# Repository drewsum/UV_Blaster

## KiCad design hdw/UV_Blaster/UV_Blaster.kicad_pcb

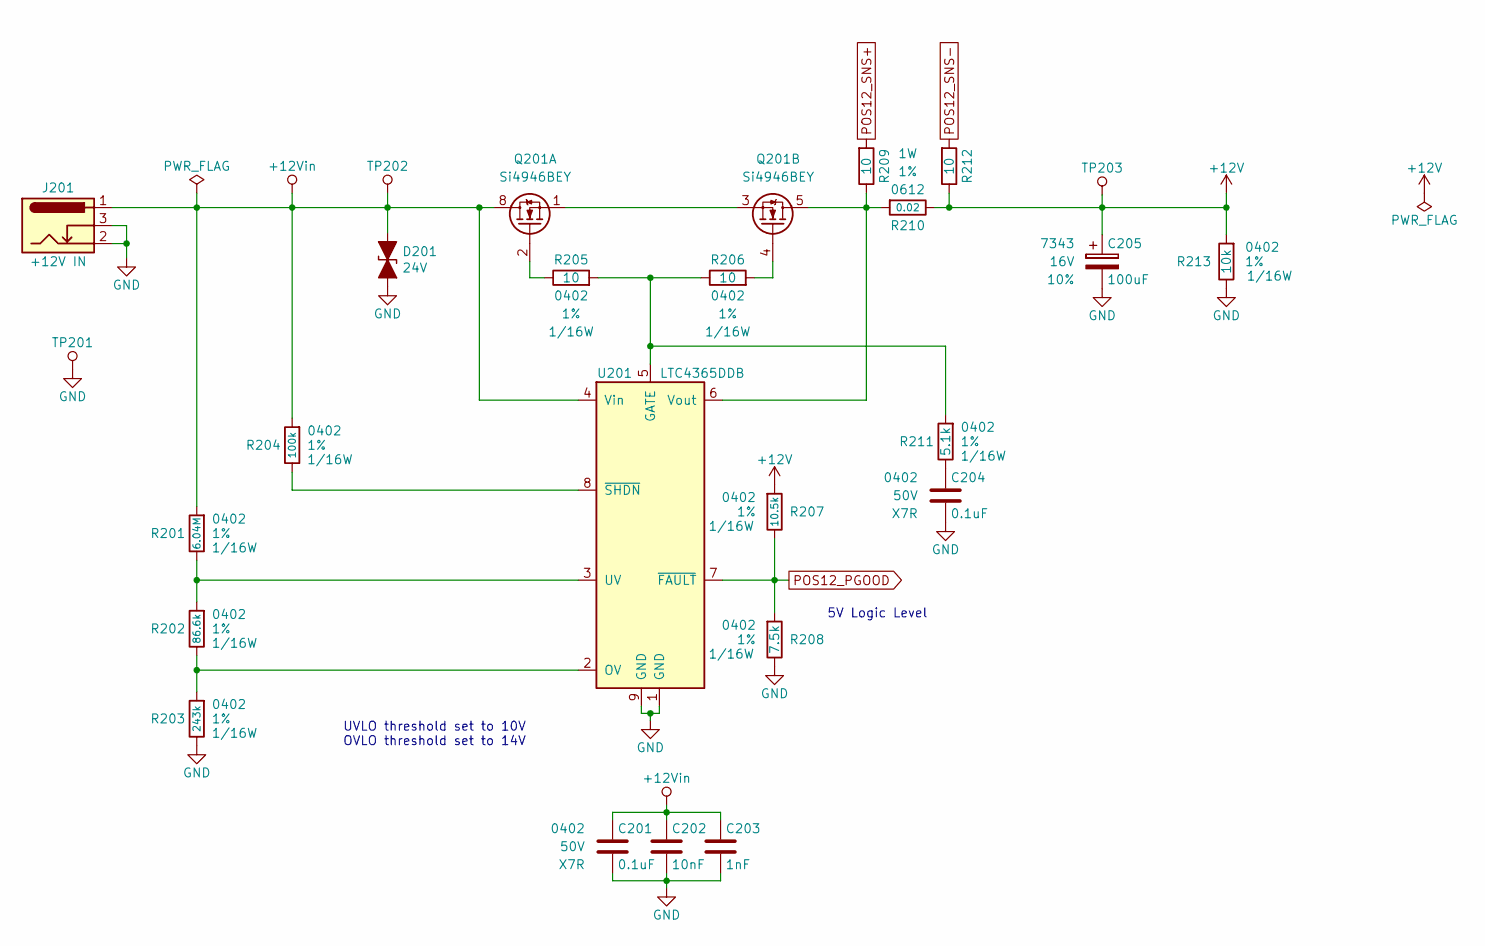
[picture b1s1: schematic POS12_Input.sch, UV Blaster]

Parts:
C201, C204: 0.1uF; C_0402; Voltage 50V; Digi-Key PN 490-10701-1-ND
C202: 10nF; C_0402; Voltage 50V; Digi-Key PN 490-13295-1-ND
C203: 1nF; C_0402; Voltage 50V; Digi-Key PN 399-1032-1-ND
C205: 100uF; CP_Tantalum_Case-X_EIA-7343-43_Reflow; Voltage 16V; Tolerance 10%; Digi-Key PN 718-1102-1-ND
D201: 24V; D_SMA; Digi-Key PN SMAJ24CALFCT-ND
J201: +12V IN; BARREL_JACK
Q201: Si4946BEY; SOIC-8_3.9x4.9mm_P1.27mm; Digi-Key PN SI4946BEY-T1-E3CT-ND
R201: 6.04M; R_0402; Tolerance 1%; Digi-Key PN 541-CRCW04026M04FKEDCT-ND
R202: 86.6k; R_0402; Tolerance 1%; Digi-Key PN P86.6KLCT-ND
R203: 243k; R_0402; Tolerance 1%; Digi-Key PN YAG3070CT-ND
R204: 100k; R_0402; Tolerance 1%; Digi-Key PN 311-100KLRCT-ND
R205, R206, R209, R212: 10; R_0402; Tolerance 1%; Digi-Key PN 311-10.0LRCT-ND
R207: 10.5k; R_0402; Tolerance 1%; Digi-Key PN RMCF0402FT10K5CT-ND
R208: 7.5k; R_0402; Tolerance 1%; Digi-Key PN RMCF0402FT7K50CT-ND
R210: 0.02; R_0612; Tolerance 1%; Digi-Key PN P16010CT-ND
R211: 5.1k; R_0402; Tolerance 1%; Digi-Key PN P5.10KLCT-ND
R213: 10k; R_0402; Tolerance 1%; Digi-Key PN 541-3959-1-ND
TP201: TP; Pin_Header_Angled_1x01_Pitch2.54mm
TP202, TP203: TP; Test_Point
U201: LTC4365DDB; DFN-8-1EP_2x3mm_Pitch0.5mm; Digi-Key PN LTC4365IDDB#TRMPBFCT-ND

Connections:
+12V: C205.1, R207.1, R210.2, R212.2, R213.1, TP203.1; also elsewhere on the board
+12Vin: C201.1, C202.1, C203.1, D201.1 (A1), J201.1, Q201.7 (D1), Q201.8 (D1), R201.1, R204.1, TP202.1, U201.4 (Vin)
GND: C201.2, C202.2, C203.2, C204.2, C205.2, D201.2 (A2), J201.2, J201.3, R203.2, R208.2, R213.2, TP201.1, U201.1 (GND), U201.9 (GND); also elsewhere on the board
unnamed: C204.1, R211.2
unnamed: Q201.1 (S1), Q201.3 (S2)
unnamed: Q201.2 (G1), R205.2
unnamed: Q201.4 (G2), R206.1
unnamed: Q201.5 (D2), Q201.6 (D2), R209.2, R210.1, U201.6 (Vout)
unnamed: R201.2, R202.1, U201.3 (UV)
unnamed: R202.2, R203.1, U201.2 (OV)
unnamed: R204.2, U201.8 (~SHDN)
unnamed: R205.1, R206.2, R211.1, U201.5 (GATE)
POS12_PGOOD: R207.2, R208.1, U201.7 (~FAULT); also elsewhere on the board
POS12_SNS+: R209.1; also elsewhere on the board
POS12_SNS-: R212.1; also elsewhere on the board

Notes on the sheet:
UVLO threshold set to 10V OVLO threshold set to 14V
5V Logic Level

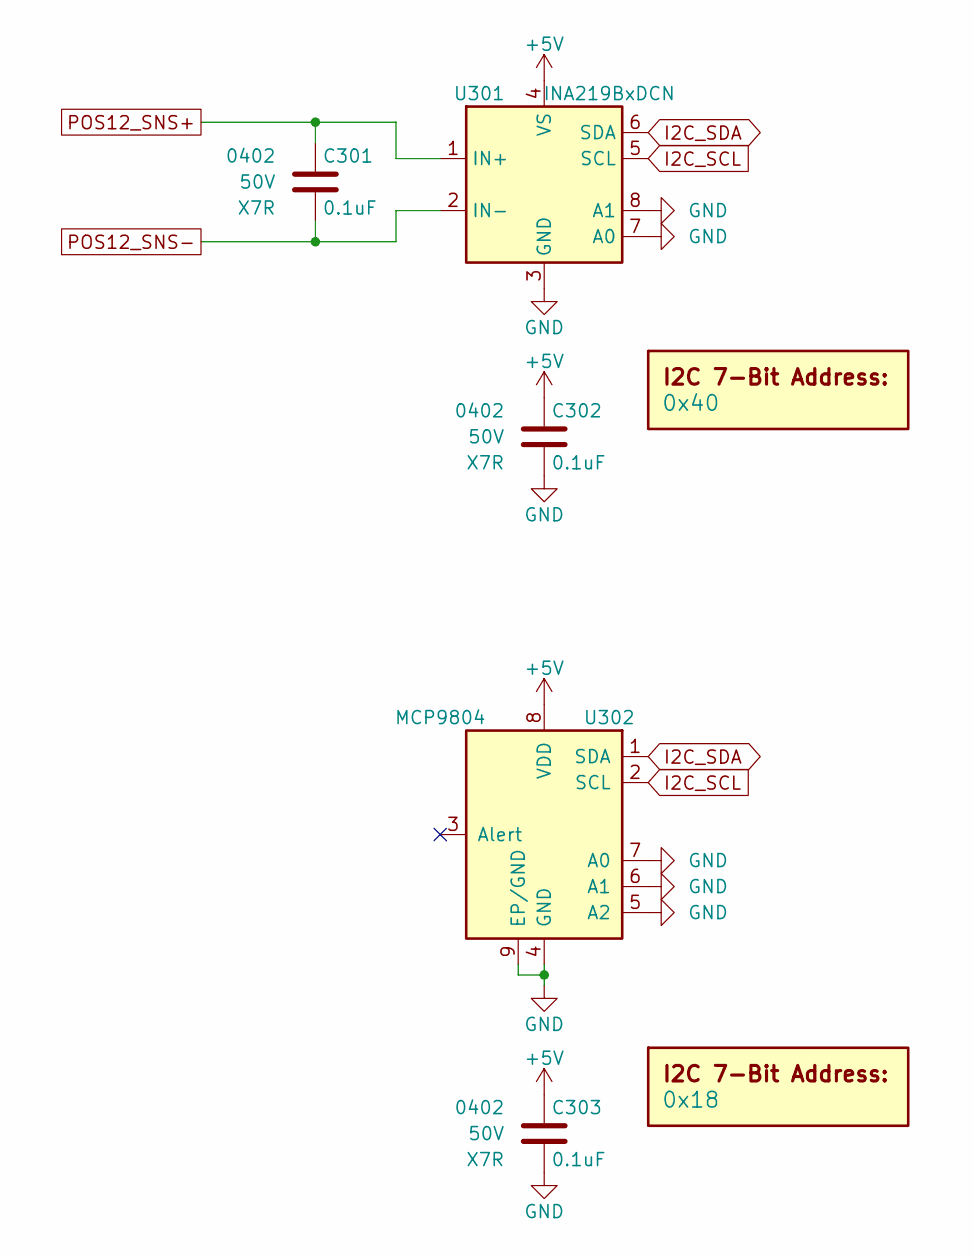
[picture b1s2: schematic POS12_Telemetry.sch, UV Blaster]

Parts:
C301, C302, C303: 0.1uF; C_0402; Voltage 50V; Digi-Key PN 490-10701-1-ND
DOC301: 0x40
DOC302: 0x18
U301: INA219BxDCN; SOT-23-8; Digi-Key PN 296-46420-1-ND
U302: MCP9804; DFN-8-1EP_3x2mm_P0.5mm_EP1.3x1.5mm; Digi-Key PN MCP9804T-E/MCCT-ND

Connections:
+5V: C302.1, C303.1, U301.4 (VS), U302.8 (VDD); also elsewhere on the board
GND: C302.2, C303.2, U301.3 (GND), U301.7 (A0), U301.8 (A1), U302.4 (GND), U302.5 (A2), U302.6 (A1), U302.7 (A0), U302.9 (EP/GND); also elsewhere on the board
I2C_SCL: U301.5 (SCL), U302.2 (SCL); also elsewhere on the board
I2C_SDA: U301.6 (SDA), U302.1 (SDA); also elsewhere on the board
POS12_SNS+: C301.1, U301.1 (IN+); also elsewhere on the board
POS12_SNS-: C301.2, U301.2 (IN-); also elsewhere on the board

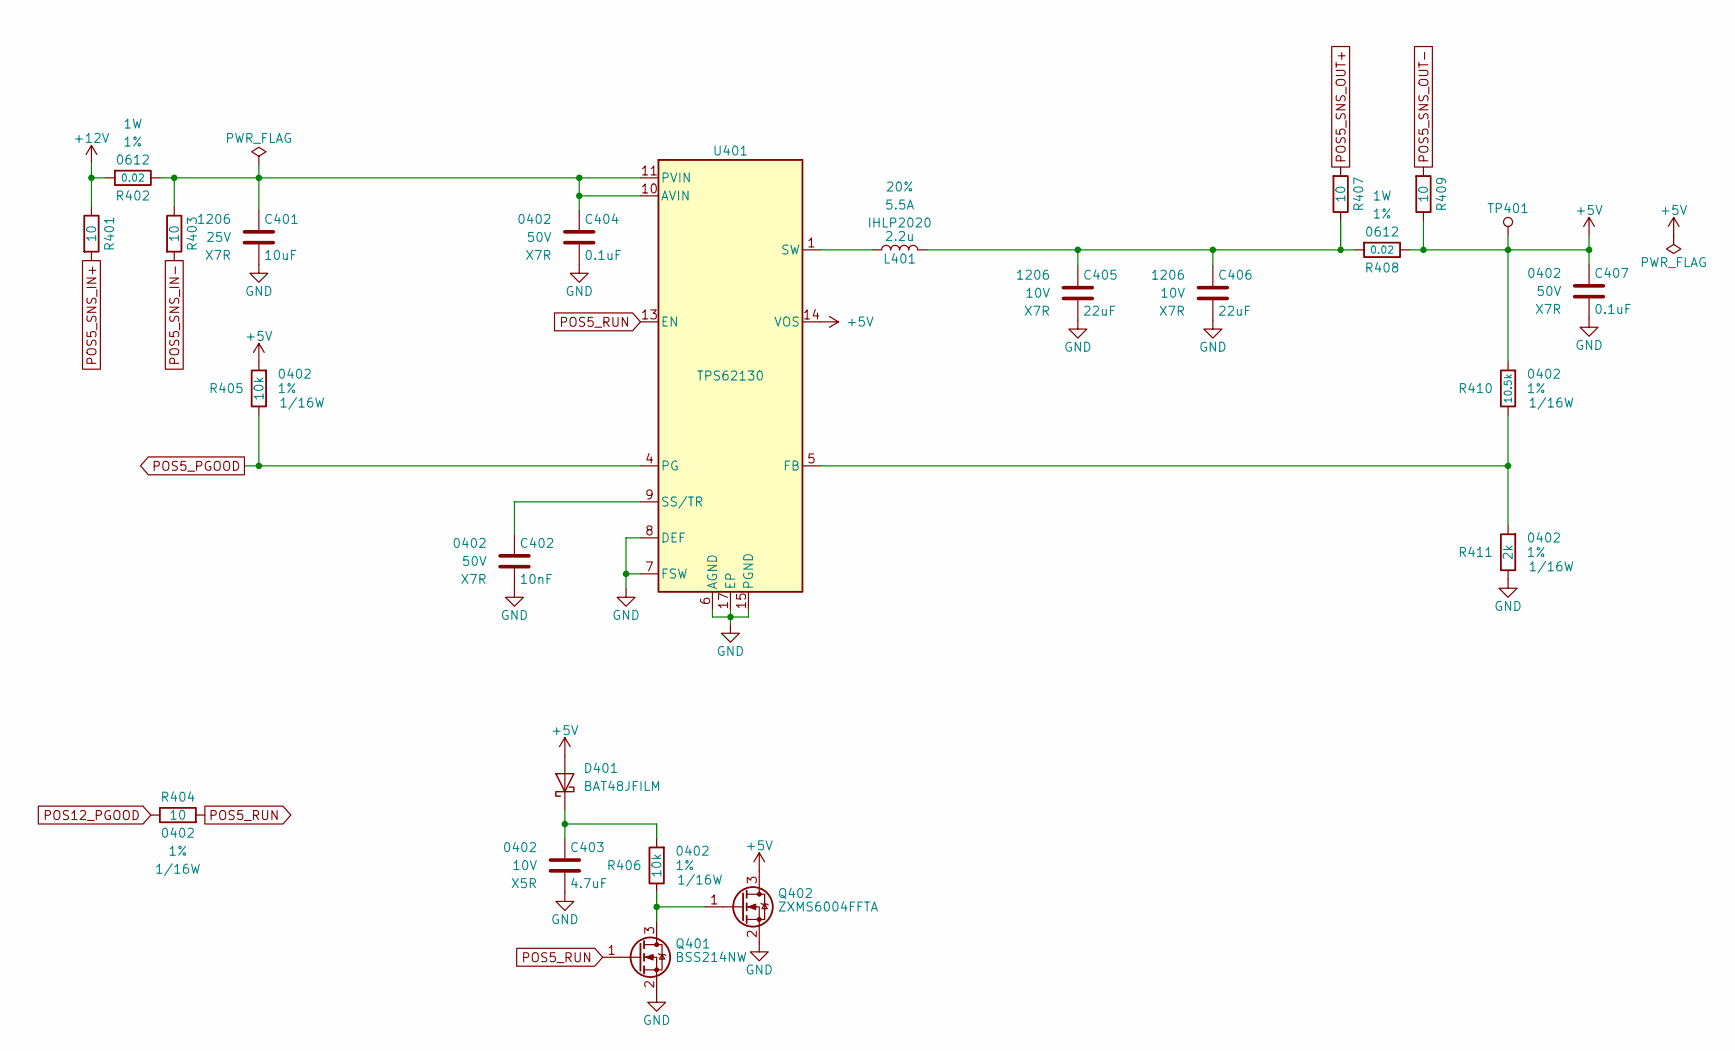
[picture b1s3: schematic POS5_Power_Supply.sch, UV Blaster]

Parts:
C401: 10uF; C_1206; Voltage 25V; Digi-Key PN 1276-7031-1-ND
C402: 10nF; C_0402; Voltage 50V; Digi-Key PN 490-13295-1-ND
C403: 4.7uF; C_0402; Voltage 10V; Digi-Key PN 490-14306-1-ND
C404, C407: 0.1uF; C_0402; Voltage 50V; Digi-Key PN 490-10701-1-ND
C405, C406: 22uF; C_1206; Voltage 10V; Digi-Key PN 1276-3148-1-ND
D401: BAT48JFILM; D_SOD-323; Digi-Key PN 497-5711-1-ND
L401: 2.2u; L_Vishay_IHLP-2020; Tolerance 20%; Digi-Key PN 541-1236-1-ND
Q401: BSS214NW; SOT-323_SC-70; Digi-Key PN BSS214NWH6327XTSA1CT-ND
Q402: ZXMS6004FFTA; SOT-23; Digi-Key PN ZXMS6004FFCT-ND
R401, R403, R404, R407, R409: 10; R_0402; Tolerance 1%; Digi-Key PN 311-10.0LRCT-ND
R402, R408: 0.02; R_0612; Tolerance 1%; Digi-Key PN P16010CT-ND
R405, R406: 10k; R_0402; Tolerance 1%; Digi-Key PN 541-3959-1-ND
R410: 10.5k; R_0402; Tolerance 1%; Digi-Key PN RMCF0402FT10K5CT-ND
R411: 2k; R_0402; Tolerance 1%; Digi-Key PN 311-2KLRCT-ND
TP401: TP; Test_Point
U401: TPS62130; QFN-16-1EP_3x3mm_Pitch0.5mm; Digi-Key PN 296-37878-1-ND

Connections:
+5V: C407.1, D401.2 (A), Q402.3 (D), R405.1, R408.2, R409.2, R410.1, TP401.1, U401.14 (VOS); also elsewhere on the board
+12V: R401.2, R402.1; also elsewhere on the board
GND: C401.2, C402.2, C403.2, C404.2, C405.2, C406.2, C407.2, Q401.2 (S), Q402.2 (S), R411.2, U401.6 (AGND), U401.7 (FSW), U401.8 (DEF), U401.15 (PGND), U401.16 (PGND), U401.17 (EP); also elsewhere on the board
unnamed: C401.1, C404.1, R402.2, R403.2, U401.10 (AVIN), U401.11 (PVIN), U401.12 (PVIN)
unnamed: C402.1, U401.9 (SS/TR)
unnamed: C403.1, D401.1 (K), R406.1
unnamed: C405.1, C406.1, L401.2, R407.2, R408.1
unnamed: L401.1, U401.1 (SW), U401.2 (SW), U401.3 (SW)
unnamed: Q401.3 (D), Q402.1 (G), R406.2
unnamed: R410.2, R411.1, U401.5 (FB)
POS5_PGOOD: R405.2, U401.4 (PG); also elsewhere on the board
POS5_RUN: Q401.1 (G), R404.1, U401.13 (EN)
POS5_SNS_IN+: R401.1; also elsewhere on the board
POS5_SNS_IN-: R403.1; also elsewhere on the board
POS5_SNS_OUT+: R407.1; also elsewhere on the board
POS5_SNS_OUT-: R409.1; also elsewhere on the board
POS12_PGOOD: R404.2; also elsewhere on the board

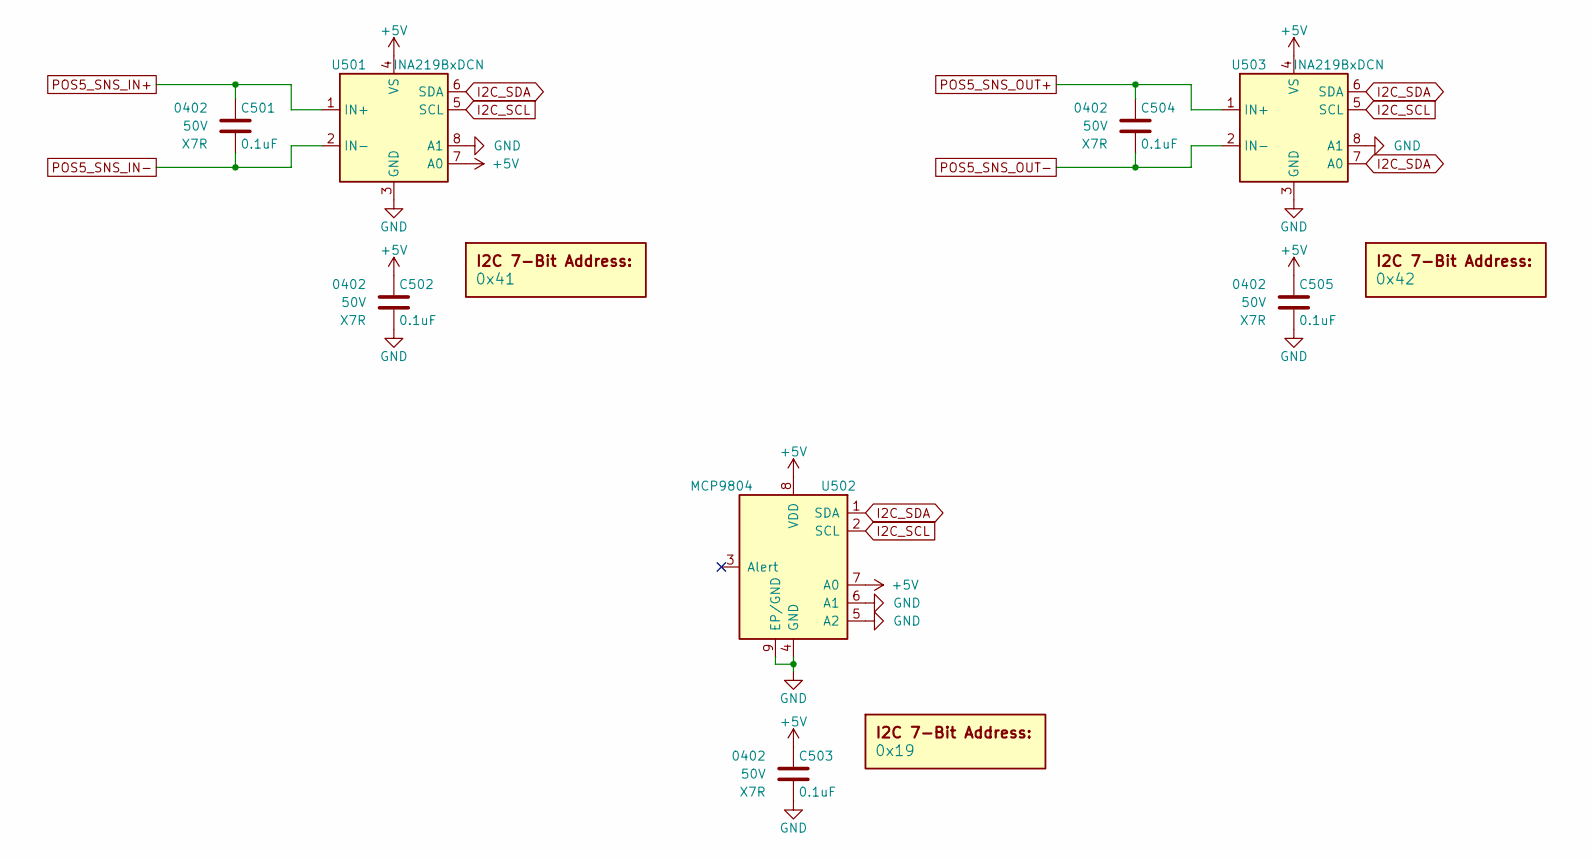
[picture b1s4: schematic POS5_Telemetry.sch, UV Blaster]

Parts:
C501, C502, C503, C504, C505: 0.1uF; C_0402; Voltage 50V; Digi-Key PN 490-10701-1-ND
DOC501: 0x41
DOC502: 0x19
DOC503: 0x42
U501, U503: INA219BxDCN; SOT-23-8; Digi-Key PN 296-46420-1-ND
U502: MCP9804; DFN-8-1EP_3x2mm_P0.5mm_EP1.3x1.5mm; Digi-Key PN MCP9804T-E/MCCT-ND

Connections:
+5V: C502.1, C503.1, C505.1, U501.4 (VS), U501.7 (A0), U502.7 (A0), U502.8 (VDD), U503.4 (VS); also elsewhere on the board
GND: C502.2, C503.2, C505.2, U501.3 (GND), U501.8 (A1), U502.4 (GND), U502.5 (A2), U502.6 (A1), U502.9 (EP/GND), U503.3 (GND), U503.8 (A1); also elsewhere on the board
I2C_SCL: U501.5 (SCL), U502.2 (SCL), U503.5 (SCL); also elsewhere on the board
I2C_SDA: U501.6 (SDA), U502.1 (SDA), U503.6 (SDA), U503.7 (A0); also elsewhere on the board
POS5_SNS_IN+: C501.1, U501.1 (IN+); also elsewhere on the board
POS5_SNS_IN-: C501.2, U501.2 (IN-); also elsewhere on the board
POS5_SNS_OUT+: C504.1, U503.1 (IN+); also elsewhere on the board
POS5_SNS_OUT-: C504.2, U503.2 (IN-); also elsewhere on the board

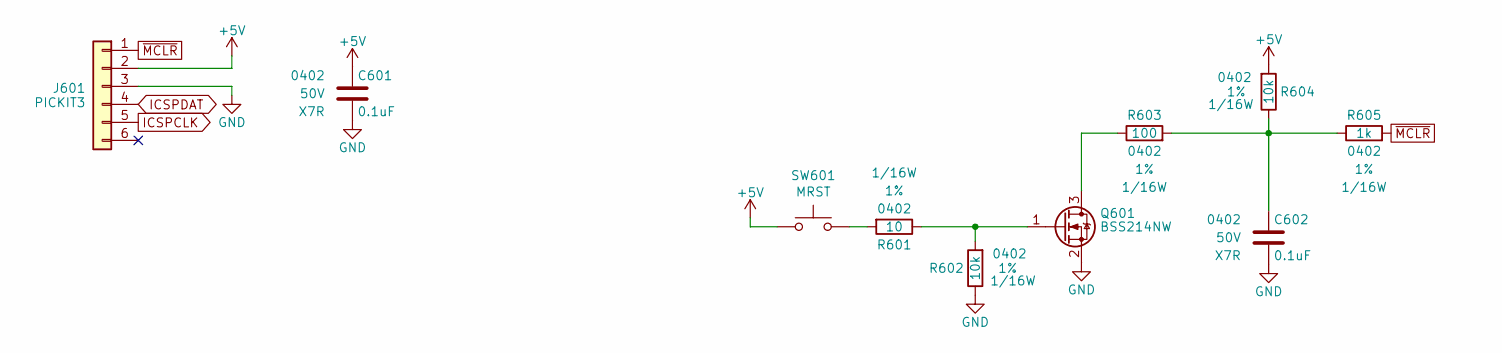
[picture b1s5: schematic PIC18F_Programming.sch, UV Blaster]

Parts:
C601, C602: 0.1uF; C_0402; Voltage 50V; Digi-Key PN 490-10701-1-ND
J601: PICKIT3; PICKIT3_Header
Q601: BSS214NW; SOT-323_SC-70; Digi-Key PN BSS214NWH6327XTSA1CT-ND
R601: 10; R_0402; Tolerance 1%; Digi-Key PN 311-10.0LRCT-ND
R602, R604: 10k; R_0402; Tolerance 1%; Digi-Key PN 541-3959-1-ND
R603: 100; R_0402; Tolerance 1%; Digi-Key PN 311-100LRCT-ND
R605: 1k; R_0402; Tolerance 1%; Digi-Key PN P1.00KLCT-ND
SW601: MRST; SW_PUSH_6mm

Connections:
+5V: C601.1, J601.2, R604.1, SW601.1; also elsewhere on the board
GND: C601.2, C602.2, J601.3, Q601.2 (S), R602.2; also elsewhere on the board
ICSPCLK: J601.5; also elsewhere on the board
ICSPDAT: J601.4; also elsewhere on the board
unnamed: C602.1, R603.1, R604.2, R605.2
unnamed: Q601.1 (G), R601.2, R602.1
unnamed: Q601.3 (D), R603.2
unnamed: R601.1, SW601.2
~MCLR: J601.1, R605.1; also elsewhere on the board

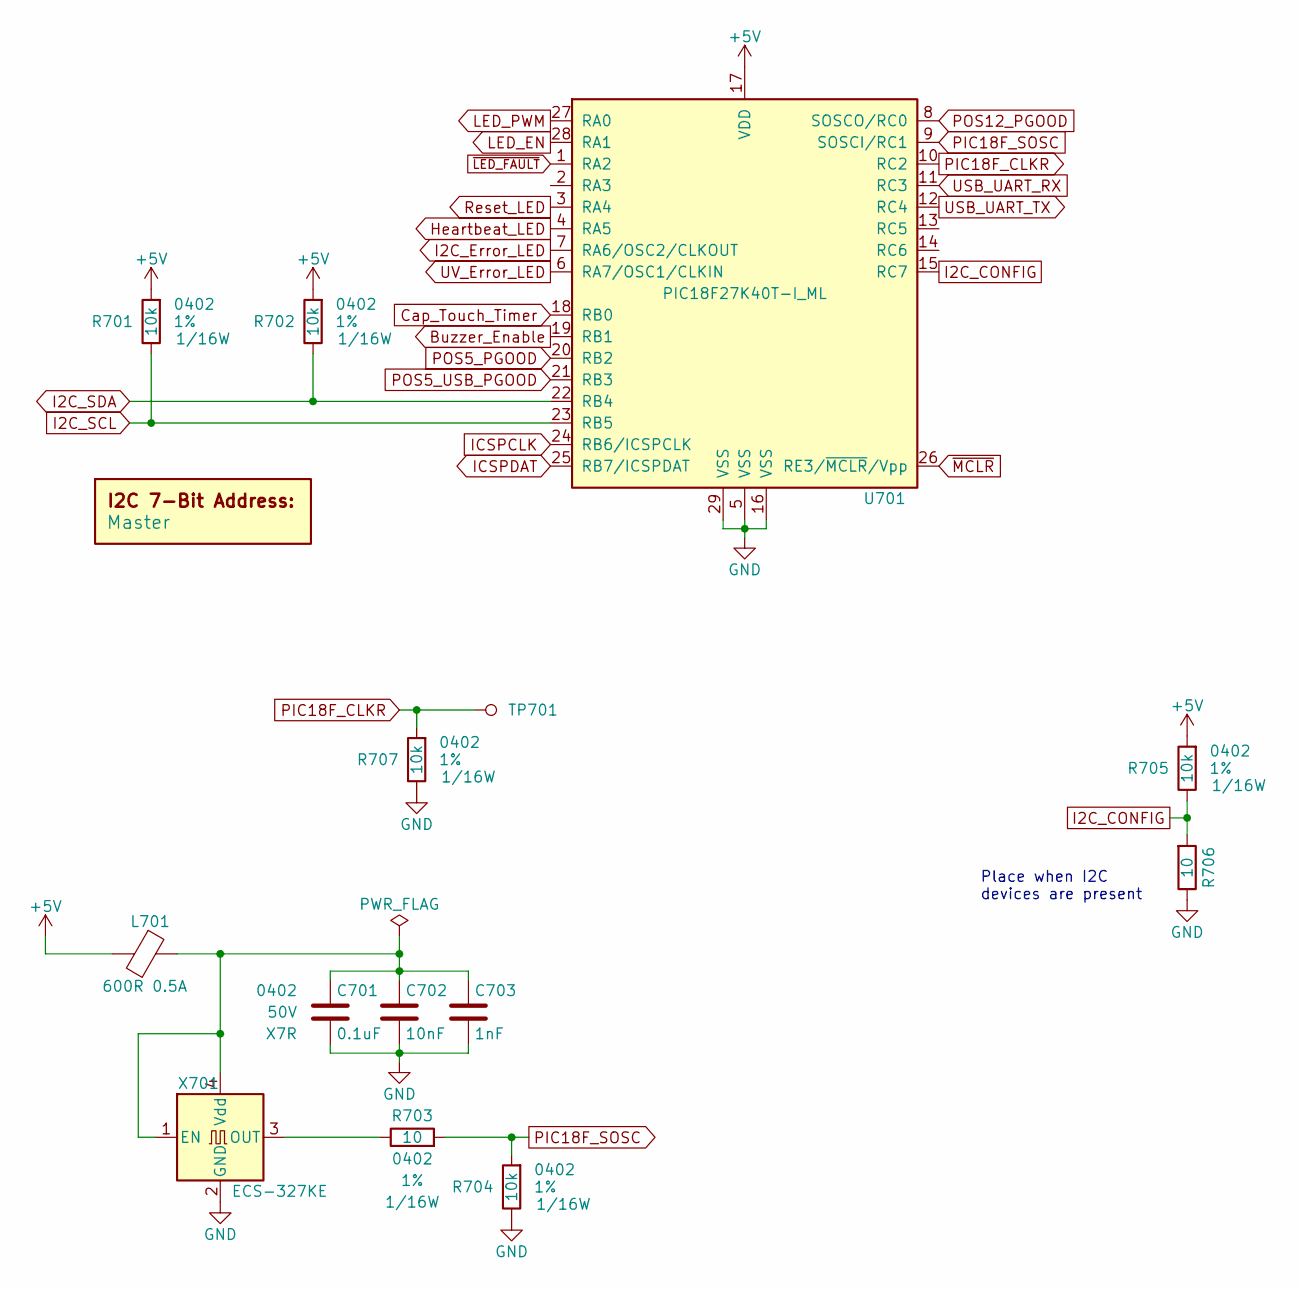
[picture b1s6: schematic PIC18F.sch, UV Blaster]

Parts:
C701: 0.1uF; C_0402; Voltage 50V; Digi-Key PN 490-10701-1-ND
C702: 10nF; C_0402; Voltage 50V; Digi-Key PN 490-13295-1-ND
C703: 1nF; C_0402; Voltage 50V; Digi-Key PN 399-1032-1-ND
DOC701: Master
L701: 600R 0.5A; L_0402; Digi-Key PN 490-16584-1-ND
R701, R702, R704, R705, R707: 10k; R_0402; Tolerance 1%; Digi-Key PN 541-3959-1-ND
R703, R706: 10; R_0402; Tolerance 1%; Digi-Key PN 311-10.0LRCT-ND
TP701: TP; Test_Point
U701: PIC18F27K40T-I_ML; QFN-28-1EP_6x6mm_Pitch0.65mm; Digi-Key PN PIC18F27K40T-I/MLCT-ND
X701: ECS-327KE; Digi-Key PN XC1751CT-ND

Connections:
+5V: L701.2, R701.1, R702.1, R705.1, U701.17 (VDD); also elsewhere on the board
Buzzer_Enable: U701.19 (RB1); also elsewhere on the board
Cap_Touch_Timer: U701.18 (RB0); also elsewhere on the board
GND: C701.2, C702.2, C703.2, R704.2, R706.2, R707.2, U701.5 (VSS), U701.16 (VSS), U701.29 (VSS), X701.2 (GND); also elsewhere on the board
Heartbeat_LED: U701.4 (RA5); also elsewhere on the board
I2C_CONFIG: R705.2, R706.1, U701.15 (RC7)
I2C_Error_LED: U701.7 (RA6/OSC2/CLKOUT); also elsewhere on the board
I2C_SCL: R701.2, U701.23 (RB5); also elsewhere on the board
I2C_SDA: R702.2, U701.22 (RB4); also elsewhere on the board
ICSPCLK: U701.24 (RB6/ICSPCLK); also elsewhere on the board
ICSPDAT: U701.25 (RB7/ICSPDAT); also elsewhere on the board
LED_EN: U701.28 (RA1); also elsewhere on the board
LED_PWM: U701.27 (RA0); also elsewhere on the board
unnamed: C701.1, C702.1, C703.1, L701.1, X701.1 (EN), X701.4 (Vdd)
unnamed: R703.2, X701.3 (OUT)
PIC18F_CLKR: R707.1, TP701.1, U701.10 (RC2)
PIC18F_SOSC: R703.1, R704.1, U701.9 (SOSCI/RC1)
POS5_PGOOD: U701.20 (RB2); also elsewhere on the board
POS5_USB_PGOOD: U701.21 (RB3); also elsewhere on the board
POS12_PGOOD: U701.8 (SOSCO/RC0); also elsewhere on the board
Reset_LED: U701.3 (RA4); also elsewhere on the board
USB_UART_RX: U701.11 (RC3); also elsewhere on the board
USB_UART_TX: U701.12 (RC4); also elsewhere on the board
UV_Error_LED: U701.6 (RA7/OSC1/CLKIN); also elsewhere on the board
~LED_FAULT: U701.1 (RA2); also elsewhere on the board
~MCLR: U701.26 (RE3/~MCLR~/Vpp); also elsewhere on the board

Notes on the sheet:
Place when I2C devices are present

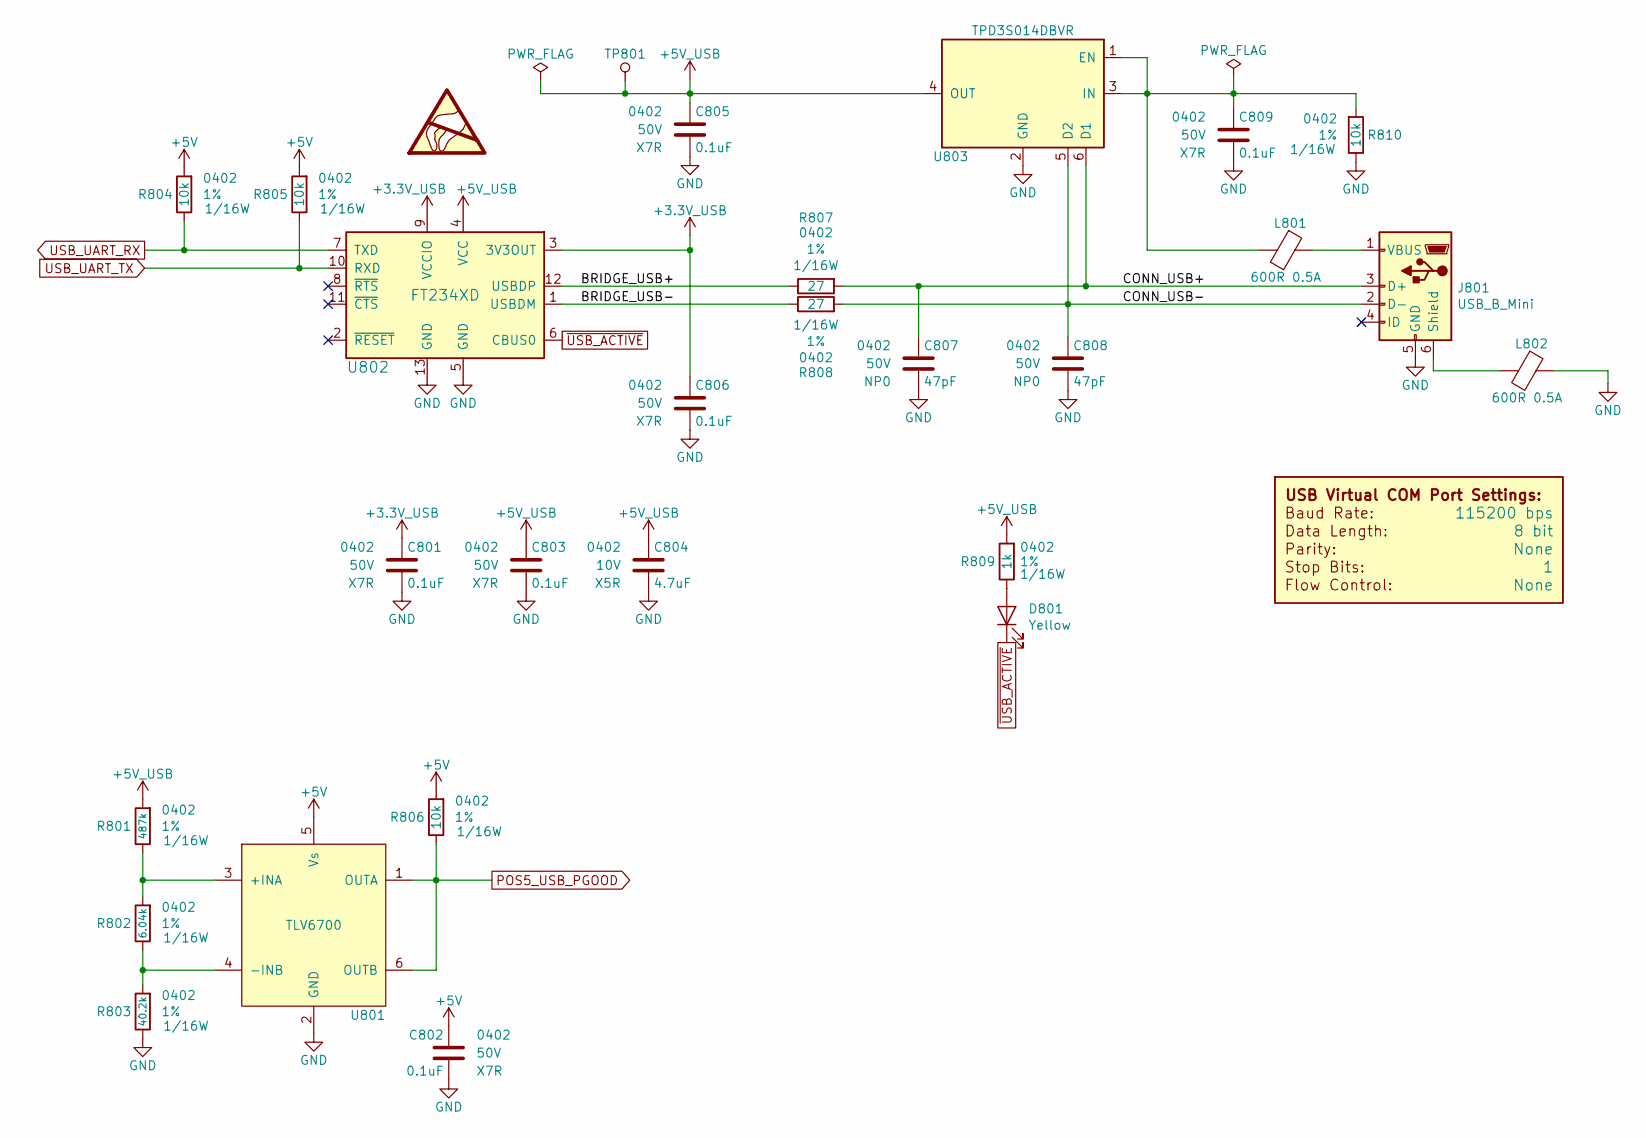
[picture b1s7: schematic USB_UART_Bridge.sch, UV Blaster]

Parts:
C801, C802, C803, C805, C806, C809: 0.1uF; C_0402; Voltage 50V; Digi-Key PN 490-10701-1-ND
C804: 4.7uF; C_0402; Voltage 10V; Digi-Key PN 490-14306-1-ND
C807, C808: 47pF; C_0402; Voltage 50V; Digi-Key PN 399-7796-1-ND
D801: Yellow; LED_0402; Digi-Key PN 754-1809-1-ND
DOC801: COM_Port_Settings
J801: USB_B_Mini; USB_Mini-B; Digi-Key PN 732-2109-1-ND
L801, L802: 600R 0.5A; L_0402; Digi-Key PN 490-16584-1-ND
R801: 487k; R_0402; Tolerance 1%; Digi-Key PN YAG2372CT-ND
R802: 6.04k; R_0402; Tolerance 1%; Digi-Key PN RMCF0402FT6K04CT-ND
R803: 40.2k; R_0402; Tolerance 1%; Digi-Key PN P40.2KLCT-ND
R804, R805, R806, R810: 10k; R_0402; Tolerance 1%; Digi-Key PN 541-3959-1-ND
R807, R808: 27; R_0402; Tolerance 1%; Digi-Key PN P27.0LCT-ND
R809: 1k; R_0402; Tolerance 1%; Digi-Key PN P1.00KLCT-ND
TP801: TP; Test_Point
U801: TLV6700; SOT-23-6; Digi-Key PN 296-51696-1-ND
U802: FT234XD; DFN-12-1EP_3x3mm_Pitch0.45mm; Digi-Key PN 768-1178-1-ND
U803: TPD3S014DBVR; SOT-23-6; Digi-Key PN 296-38835-1-ND

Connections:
+3.3V_USB: C801.1, C806.1, U802.3 (3V3OUT), U802.9 (VCCIO)
+5V: C802.1, R804.1, R805.1, R806.1, U801.5 (Vs); also elsewhere on the board
+5V_USB: C803.1, C804.1, C805.1, R801.1, R809.1, TP801.1, U802.4 (VCC), U803.4 (OUT)
/USB UART Bridge/BRIDGE_USB+: R807.2, U802.12 (USBDP)
/USB UART Bridge/BRIDGE_USB-: R808.2, U802.1 (USBDM)
/USB UART Bridge/CONN_USB+: C807.1, J801.3 (D+), R807.1, U803.6 (D1)
/USB UART Bridge/CONN_USB-: C808.1, J801.2 (D-), R808.1, U803.5 (D2)
GND: C801.2, C802.2, C803.2, C804.2, C805.2, C806.2, C807.2, C808.2, C809.2, J801.5 (GND), L802.1, R803.2, R810.2, U801.2 (GND), U802.5 (GND), U802.13 (GND), U803.2 (GND); also elsewhere on the board
unnamed: C809.1, L801.2, R810.1, U803.1 (EN), U803.3 (IN)
unnamed: D801.2 (A), R809.2
unnamed: J801.1 (VBUS), L801.1
unnamed: J801.6 (Shield), L802.2
unnamed: R801.2, R802.1, U801.3 (+INA)
unnamed: R802.2, R803.1, U801.4 (-INB)
POS5_USB_PGOOD: R806.2, U801.1 (OUTA), U801.6 (OUTB); also elsewhere on the board
USB_UART_RX: R804.2, U802.7 (TXD); also elsewhere on the board
USB_UART_TX: R805.2, U802.10 (RXD); also elsewhere on the board
~USB_ACTIVE: D801.1 (K), U802.6 (CBUS0)

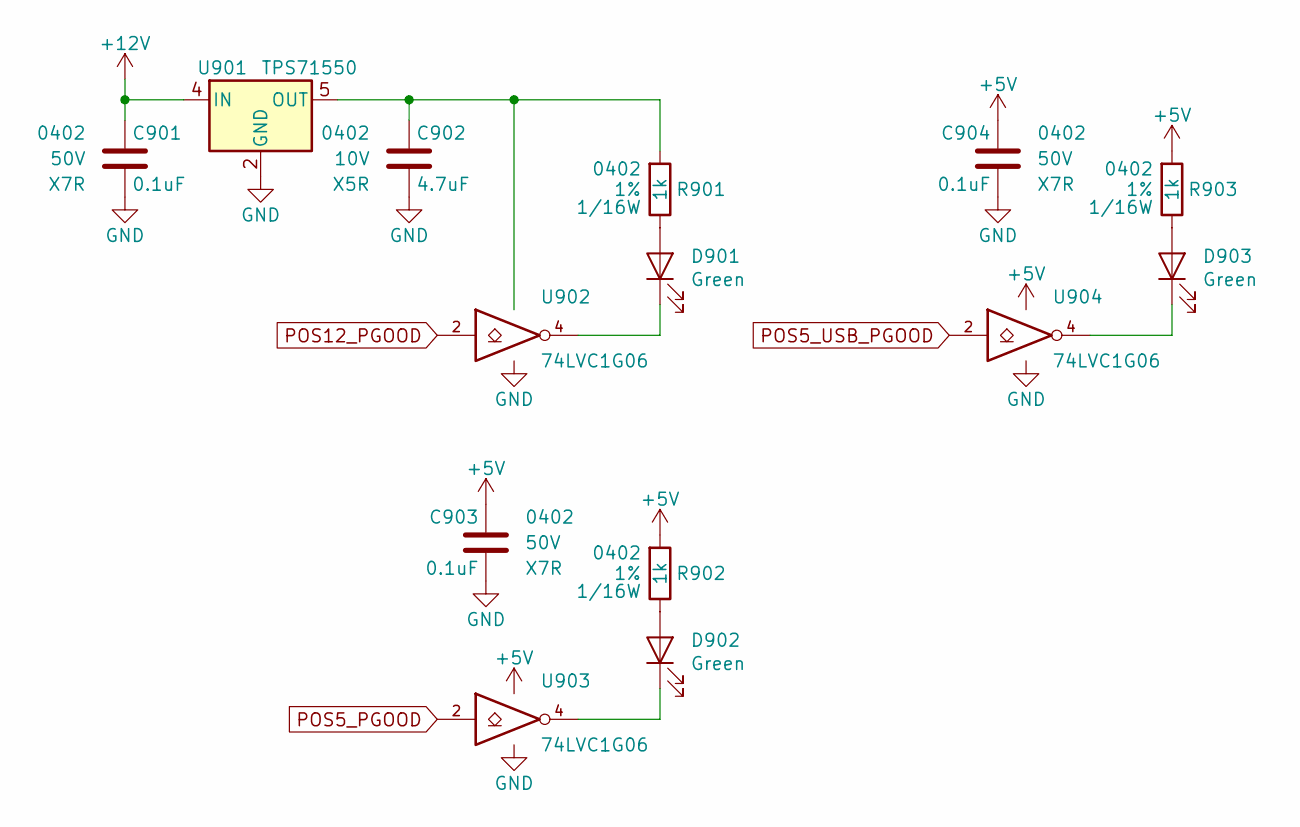
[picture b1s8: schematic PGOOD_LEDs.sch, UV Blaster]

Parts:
C901, C903, C904: 0.1uF; C_0402; Voltage 50V; Digi-Key PN 490-10701-1-ND
C902: 4.7uF; C_0402; Voltage 10V; Digi-Key PN 490-14306-1-ND
D901, D902, D903: Green; LED_0402; Digi-Key PN 754-1815-1-ND
R901, R902, R903: 1k; R_0402; Tolerance 1%; Digi-Key PN P1.00KLCT-ND
U901: TPS71550; SOT-353_SC-70-5; Digi-Key PN 296-15046-1-ND
U902, U903, U904: 74LVC1G06; SOT-353_SC-70-5; Digi-Key PN 296-8484-1-ND

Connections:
+5V: C903.1, C904.1, R902.1, R903.1, U903.5 (VCC), U904.5 (VCC); also elsewhere on the board
+12V: C901.1, U901.4 (IN); also elsewhere on the board
GND: C901.2, C902.2, C903.2, C904.2, U901.2 (GND), U902.3 (GND), U903.3 (GND), U904.3 (GND); also elsewhere on the board
unnamed: C902.1, R901.1, U901.5 (OUT), U902.5 (VCC)
unnamed: D901.1 (K), U902.4
unnamed: D901.2 (A), R901.2
unnamed: D902.1 (K), U903.4
unnamed: D902.2 (A), R902.2
unnamed: D903.1 (K), U904.4
unnamed: D903.2 (A), R903.2
POS5_PGOOD: U903.2; also elsewhere on the board
POS5_USB_PGOOD: U904.2; also elsewhere on the board
POS12_PGOOD: U902.2; also elsewhere on the board

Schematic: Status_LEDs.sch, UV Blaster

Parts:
C1001, C1002, C1003, C1004: 0.1uF; C_0402; Voltage 50V; Digi-Key PN 490-10701-1-ND
D1001: Green; LED_0402; Digi-Key PN 754-1815-1-ND
D1002, D1003, D1004: Red; LED_0402; Digi-Key PN 754-1812-1-ND
R1001, R1003, R1005, R1007: 10k; R_0402; Tolerance 1%; Digi-Key PN 541-3959-1-ND
R1002, R1004, R1006, R1008: 1k; R_0402; Tolerance 1%; Digi-Key PN P1.00KLCT-ND
U1001, U1002, U1003, U1004: 74LVC1G06; SOT-353_SC-70-5; Digi-Key PN 296-8484-1-ND

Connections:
+5V: C1001.1, C1002.1, C1003.1, C1004.1, R1002.1, R1003.1, R1004.1, R1006.1, R1008.1, U1001.5 (VCC), U1003.5 (VCC), U1004.5 (VCC); also elsewhere on the board
GND: C1001.2, C1002.2, C1003.2, C1004.2, R1001.2, R1005.2, R1007.2, U1001.3 (GND), U1002.3 (GND), U1003.3 (GND), U1004.3 (GND); also elsewhere on the board
Heartbeat_LED: R1001.1, U1001.2; also elsewhere on the board
I2C_Error_LED: R1007.1, U1004.2; also elsewhere on the board
unnamed: D1001.1 (K), U1001.4
unnamed: D1001.2 (A), R1002.2
unnamed: D1002.1 (K), U1002.4
unnamed: D1002.2 (A), R1004.2
unnamed: D1003.1 (K), U1003.4
unnamed: D1003.2 (A), R1006.2
unnamed: D1004.1 (K), U1004.4
unnamed: D1004.2 (A), R1008.2
Reset_LED: R1003.2, U1002.2; also elsewhere on the board
UV_Error_LED: R1005.1, U1003.2; also elsewhere on the board

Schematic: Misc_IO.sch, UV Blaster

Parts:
BZ1101: CST-931RP; MagneticBuzzer_CUI_CST-931RP-A; Digi-Key PN 102-1461-ND
C1101, C1102, C1104, C1105, C1107, C1108: 0.1uF; C_0402; Voltage 50V; Digi-Key PN 490-10701-1-ND
C1103: 10nF; C_0402; Voltage 50V; Digi-Key PN 490-13295-1-ND
C1106: 10uF; C_0402; Voltage 10V; Digi-Key PN 1276-6830-1-ND
D1101: BAT48JFILM; D_SOD-323; Digi-Key PN 497-5711-1-ND
DOC1101: 0x1A
Q1101: BSS214NW; SOT-323_SC-70; Digi-Key PN BSS214NWH6327XTSA1CT-ND
R1101: 1.07M; R_0402; Tolerance 1%; Digi-Key PN RMCF0402FT1M07CT-ND
R1102, R1104, R1106, R1107, R1108: 10k; R_0402; Tolerance 1%; Digi-Key PN 541-3959-1-ND
R1103: 499; R_0402; Tolerance 1%; Digi-Key PN P499LCT-ND
R1105: 10; R_0402; Tolerance 1%; Digi-Key PN 311-10.0LRCT-ND
SW1101: Cap_Touch; Capacitive_Touch_Pad
U1101: LTC6900; SOT-23-5; Digi-Key PN LTC6900CS5#TRMPBFCT-ND
U1102: TLV71333PDBV; SOT-23-5; Digi-Key PN 296-35591-1-ND
U1103: 74LVC1G08; SOT-353_SC-70-5; Digi-Key PN 296-11602-1-ND
U1104: AT42QT1010-TSHR; SOT-23-6; Digi-Key PN AT42QT1010-TSHRCT-ND
U1105: 74LVC1G17; SOT-353_SC-70-5; Digi-Key PN 296-11934-1-ND
U1106: MCP9804; DFN-8-1EP_3x2mm_P0.5mm_EP1.3x1.5mm; Digi-Key PN MCP9804T-E/MCCT-ND

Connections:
+5V: BZ1101.1 (-), C1101.1, C1102.1, C1104.1, C1107.1, C1108.1, D1101.1 (K), R1101.1, U1101.1 (V+), U1101.4 (DIV), U1102.1 (IN), U1102.3 (EN), U1103.5 (VCC), U1105.5 (VCC), U1106.6 (A1), U1106.8 (VDD); also elsewhere on the board
Buzzer_Enable: R1104.1, U1103.2; also elsewhere on the board
Cap_Touch_Timer: U1105.4; also elsewhere on the board
GND: C1101.2, C1102.2, C1104.2, C1105.2, C1106.2, C1107.2, C1108.2, Q1101.2 (S), R1102.2, R1104.2, R1106.2, R1107.2, U1101.2 (GND), U1102.2 (GND), U1103.3 (GND), U1104.2 (VSS), U1105.3 (GND), U1106.4 (GND), U1106.5 (A2), U1106.7 (A0), U1106.9 (EP/GND); also elsewhere on the board
I2C_SCL: U1106.2 (SCL); also elsewhere on the board
I2C_SDA: U1106.1 (SDA); also elsewhere on the board
unnamed: BZ1101.2 (+), D1101.2 (A), Q1101.3 (D)
unnamed: C1103.1, U1104.4 (SNS)
unnamed: C1103.2, R1103.2, U1104.3 (SNSK)
unnamed: C1105.1, U1102.5 (OUT), U1104.5 (VDD), U1104.6 (SYNC)
unnamed: C1106.1, R1108.1, U1105.2
unnamed: Q1101.1 (G), R1105.1, R1107.1
unnamed: R1101.2, U1101.3 (SET)
unnamed: R1102.1, U1101.5 (OUT), U1103.1
unnamed: R1103.1, SW1101.1
unnamed: R1105.2, U1103.4
unnamed: R1106.1, R1108.2, U1104.1 (OUT)

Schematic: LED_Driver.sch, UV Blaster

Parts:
C1201, C1205: 0.1uF; C_0402; Voltage 50V; Digi-Key PN 490-10701-1-ND
C1202, C1203: 1uF; C_0402; Voltage 10V; Digi-Key PN 490-13409-1-ND
C1204: 10uF; C_1206; Voltage 25V; Digi-Key PN 490-14678-1-ND
C1206: 47pF; C_0402; Voltage 50V; Digi-Key PN 399-7796-1-ND
C1207, C1208: 4.7uF; C_1206; Voltage 100V; Digi-Key PN 490-18620-1-ND
D1201: PMEG6010CEH; D_SOD-123; Digi-Key PN 1727-3848-1-ND
DOC1201: 0x2C
L1201: 15uH; L_Vishay_IHLP-2525; Tolerance 20%; Digi-Key PN 541-2173-1-ND
R1201, R1202, R1203, R1207: 10k; R_0402; Tolerance 1%; Digi-Key PN 541-3959-1-ND
R1204: 120k; R_0402; Tolerance 1%; Digi-Key PN A129652CT-ND
R1205, R1208, R1210, R1212: 10; R_0402; Tolerance 1%; Digi-Key PN 311-10.0LRCT-ND
R1206, R1211: 0.02; R_0612; Tolerance 1%; Digi-Key PN P16010CT-ND
R1209: 16k; R_0402; Tolerance 1%; Digi-Key PN RMCF0402FT16K0CT-ND
TP1201: TP; Test_Point
U1201: LP8545; QFN-24-1EP_4x4mm_Pitch0.5mm; Digi-Key PN 296-35212-1-ND

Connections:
+5V: C1203.1, C1205.1, R1202.1, U1201.8 (VDDIO), U1201.22 (VLDO), U1201.23 (VIN); also elsewhere on the board
+12V: R1205.2, R1206.1; also elsewhere on the board
GND: C1201.2, C1202.2, C1203.2, C1204.2, C1205.2, C1206.2, C1207.2, C1208.2, R1201.2, R1203.2, R1207.2, R1209.2, U1201.1 (GND_SW), U1201.9 (GND_S), U1201.15 (GND_L), U1201.19 (VSYNC), U1201.25 (GND_PAD); also elsewhere on the board
I2C_SCL: U1201.10 (SCLK); also elsewhere on the board
I2C_SDA: U1201.11 (SDA); also elsewhere on the board
LED_EN: R1203.1, U1201.4 (EN); also elsewhere on the board
LED_PWM: R1201.1, U1201.2 (PWM); also elsewhere on the board
unnamed: C1201.1, R1204.1, U1201.20 (FILTER)
unnamed: C1202.1, R1204.2
unnamed: C1204.1, L1201.1, R1206.2, R1208.2
unnamed: C1206.1, C1207.1, C1208.1, D1201.1 (K), R1210.2, R1211.1
unnamed: D1201.2 (A), L1201.2, U1201.24 (SW)
unnamed: R1207.1, U1201.5 (FSET)
unnamed: R1209.1, U1201.3 (ISET)
VLED: R1211.2, R1212.2, TP1201.1, U1201.21 (FB); also elsewhere on the board
VLED_SNS_IN+: R1205.1; also elsewhere on the board
VLED_SNS_IN-: R1208.1; also elsewhere on the board
VLED_SNS_OUT+: R1210.1; also elsewhere on the board
VLED_SNS_OUT-: R1212.1; also elsewhere on the board
~LED_FAULT: R1202.2, U1201.7 (FAULT); also elsewhere on the board
~LED_SINK_0: U1201.12 (OUT1); also elsewhere on the board
~LED_SINK_1: U1201.13 (OUT2); also elsewhere on the board
~LED_SINK_2: U1201.14 (OUT3); also elsewhere on the board
~LED_SINK_3: U1201.16 (OUT4); also elsewhere on the board
~LED_SINK_4: U1201.17 (OUT5); also elsewhere on the board
~LED_SINK_5: U1201.18 (OUT6); also elsewhere on the board

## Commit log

2020-05-03 Started schematic
2020-05-08 More sch work, netlist, part numbers, footprints
2020-05-08 Pulled in netlist into PCB
2020-05-08 Arranged input power parts
